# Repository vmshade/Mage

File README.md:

<!--
  This journal is auto generated by Hack Club Blueprint.
-->

# 3/29/2026 6 PM - Finished Schematic + Started PCB  

_Time spent: 0.7h_  

Wired up the schematic and made my own footprint for the USB connectivity. Decided to go for a clean and aesthetic "pcb finger" approach. Also started working on the PCB

# 3/29/2026 8:03 PM - Finished PCB + Started BOM  

_Time spent: 1.0h_  

Finished the PCB. Its only after i reviewed the dimensions did i realise this is one chonke boi. But its alright as long as it does what i need to. I took inspiration from the Waveshare rp2350 one.  

# 3/29/2026 8:48 PM - Uploaded Gerber to JLCPCB  

_Time spent: 0.5h_  

Uploaded gerber files to jlcpcb and created the bill of materials. Came out to around £57 including shipping which is crazy for something so small. :(

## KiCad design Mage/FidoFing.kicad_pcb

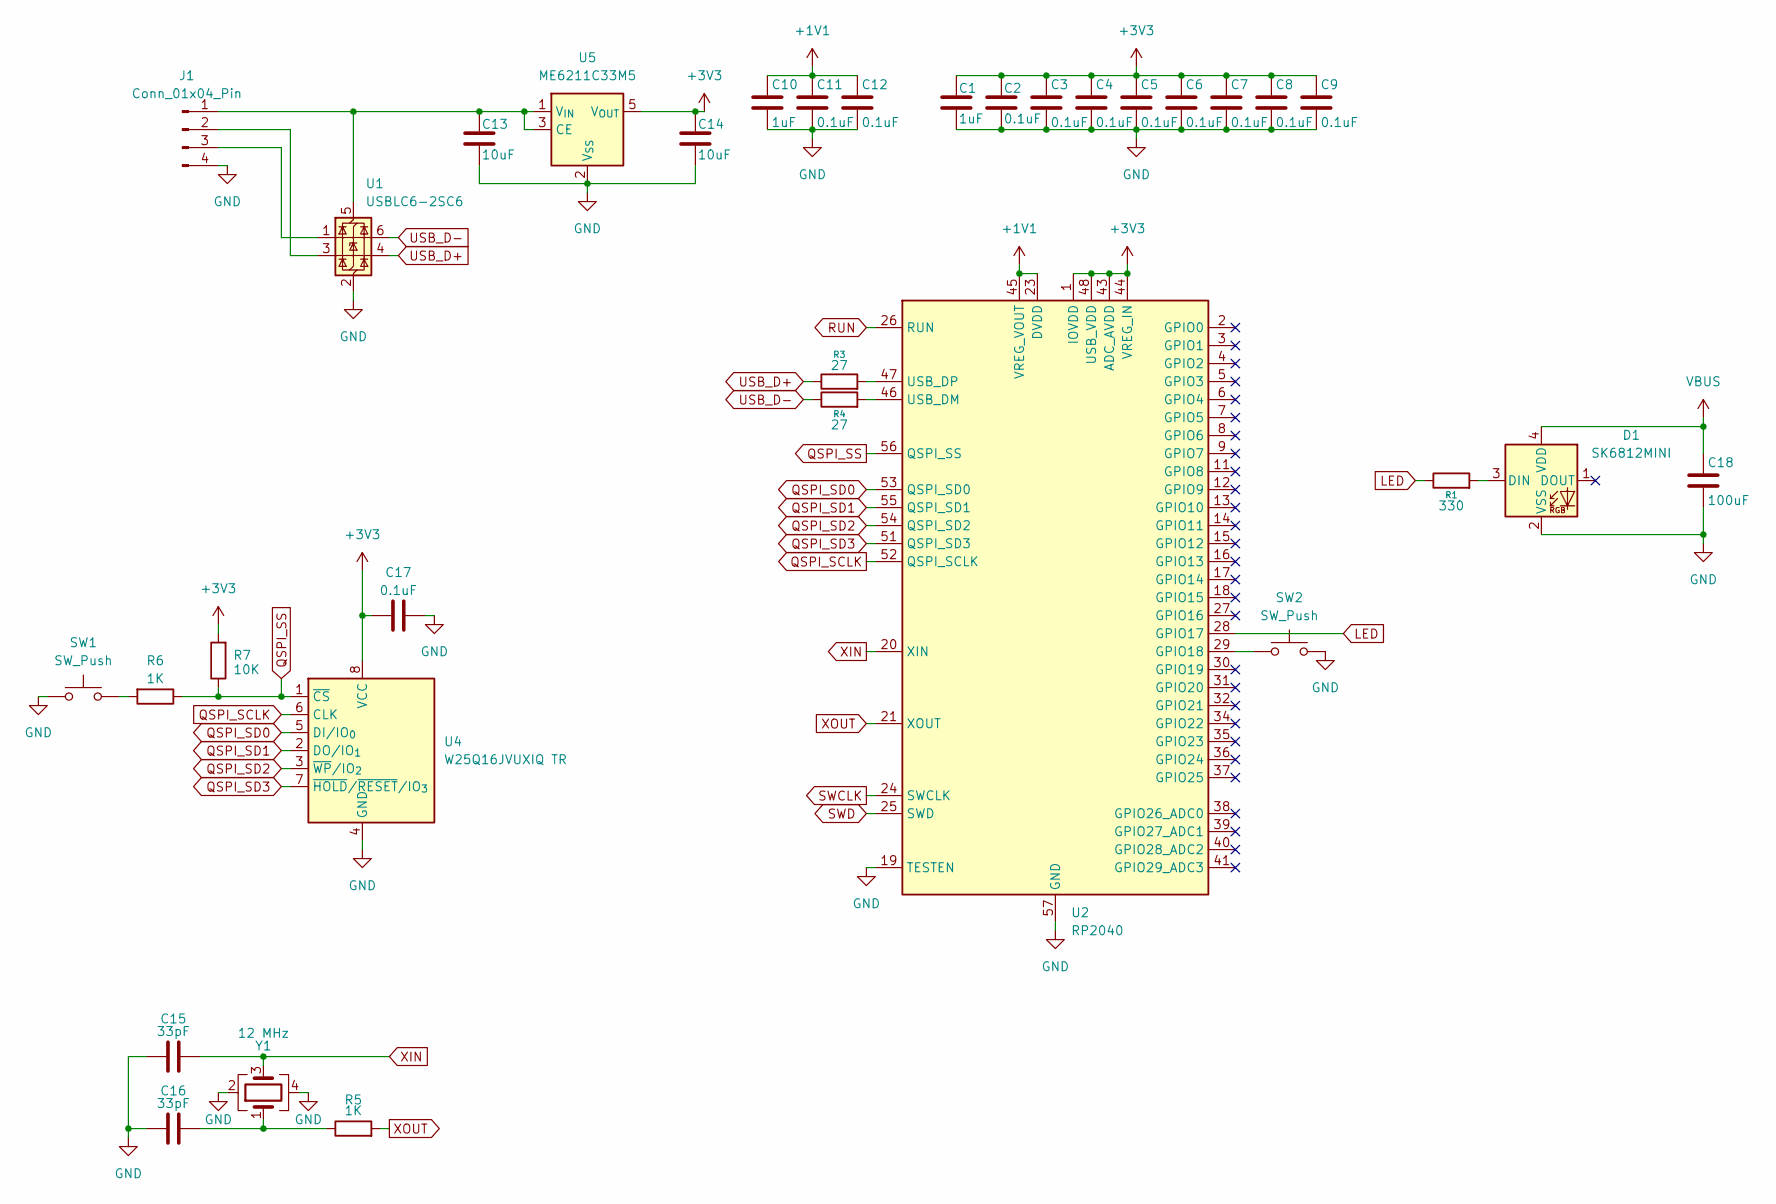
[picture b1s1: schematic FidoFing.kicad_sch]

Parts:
C1, C10: 1uF; C_0402_1005Metric
C2, C3, C4, C5, C6, C7, C8, C9, C11, C12, C17: 0.1uF; C_0402_1005Metric
C13, C14: 10uF; C_0402_1005Metric
C15, C16: 33pF; C_0402_1005Metric
C18: 100uF; C_0805_2012Metric
D1: SK6812MINI; LED_SK6812MINI_PLCC4_3.5x3.5mm_P1.75mm
J1: Conn_01x04_Pin; USB_A
R1: 330; R_0402_1005Metric
R3, R4: 27; R_0402_1005Metric
R5, R6: 1K; R_0402_1005Metric
R7: 10K; R_0402_1005Metric
SW1, SW2: SW_Push; SW_Push_SPST_NO_Alps_SKRK
U1: USBLC6-2SC6; SOT-23-6
U2: RP2040; QFN-56-1EP_7x7mm_P0.4mm_EP3.2x3.2mm
U4: W25Q16JVUXIQ TR; Winbond_USON-8-1EP_3x2mm_P0.5mm_EP0.2x1.6mm
U5: ME6211C33M5; SOT-23-5
Y1: 12 MHz; Crystal_SMD_3225-4Pin_3.2x2.5mm

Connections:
+1V1: C10.1, C11.1, C12.1, U2.23 (DVDD), U2.45 (VREG_VOUT), U2.50 (DVDD)
+3V3: C1.1, C2.1, C3.1, C4.1, C5.1, C6.1, C7.1, C8.1, C9.1, C14.1, C17.1, R7.2, U2.1 (IOVDD), U2.10 (IOVDD), U2.22 (IOVDD), U2.33 (IOVDD), U2.42 (IOVDD), U2.43 (ADC_AVDD), U2.44 (VREG_IN), U2.48 (USB_VDD), U2.49 (IOVDD), U4.8 (VCC), U5.5 (V_{OUT})
GND: C1.2, C2.2, C3.2, C4.2, C5.2, C6.2, C7.2, C8.2, C9.2, C10.2, C11.2, C12.2, C13.2, C14.2, C15.1, C16.1, C17.2, C18.2, D1.2 (VSS), J1.4, SW1.1, SW2.2, U1.2 (GND), U2.19 (TESTEN), U2.57 (GND), U4.4 (GND), U5.2 (V_{SS}), Y1.2, Y1.4
LED: R1.1, U2.28 (GPIO17)
unnamed: C16.2, R5.1, Y1.1
unnamed: D1.3 (DIN), R1.2
unnamed: C13.1, J1.1, U1.5 (VBUS), U5.1 (V_{IN}), U5.3 (CE)
unnamed: J1.2, U1.3 (I/O2)
unnamed: J1.3, U1.1 (I/O1)
unnamed: R6.2, SW1.2
unnamed: SW2.1, U2.29 (GPIO18)
unnamed: R4.2, U2.46 (USB_DM)
unnamed: R3.2, U2.47 (USB_DP)
QSPI_SCLK: U2.52 (QSPI_SCLK), U4.6 (CLK)
QSPI_SD0: U2.53 (QSPI_SD0), U4.5 (DI/IO_{0})
QSPI_SD1: U2.55 (QSPI_SD1), U4.2 (DO/IO_{1})
QSPI_SD2: U2.54 (QSPI_SD2), U4.3 (~WP/IO_{2})
QSPI_SD3: U2.51 (QSPI_SD3), U4.7 (~HOLD/~RESET/IO_{3})
QSPI_SS: R6.1, R7.1, U2.56 (QSPI_SS), U4.1 (~CS)
RUN: U2.26 (RUN)
SWCLK: U2.24 (SWCLK)
SWD: U2.25 (SWD)
USB_D+: R3.1, U1.4 (I/O2)
USB_D-: R4.1, U1.6 (I/O1)
VBUS: C18.1, D1.4 (VDD)
XIN: C15.2, U2.20 (XIN), Y1.3
XOUT: R5.2, U2.21 (XOUT)

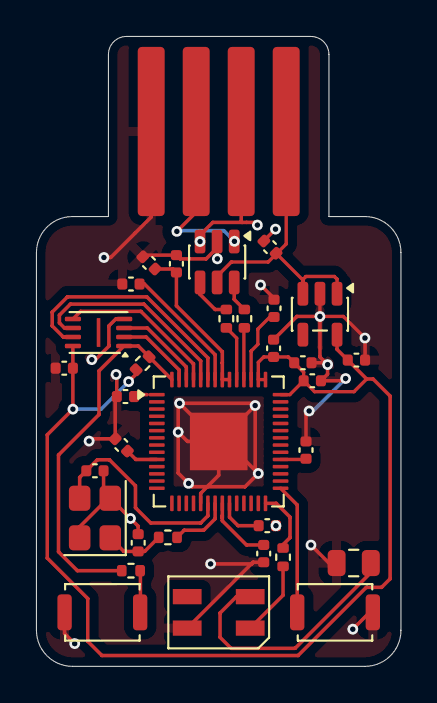
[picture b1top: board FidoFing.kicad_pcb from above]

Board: 2 copper layers, 20.3 x 35.0 mm, 33 parts (0 on the bottom side), 24 nets.

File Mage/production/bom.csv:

Designator,Footprint,Quantity,Value,LCSC Part #
"C1, C10",0402,2,1uF,
"C11, C12, C17, C2, C3, C4, C5, C6, C7, C8, C9",0402,11,0.1uF,
"C13, C14",0402,2,10uF,
"C15, C16",0402,2,33pF,
C18,0805,1,100uF,
D1,LED_SK6812MINI_PLCC4_3.5x3.5mm_P1.75mm,1,SK6812MINI,
J1,USB_A,1,Conn_01x04_Pin,
R1,0402,1,330,
"R3, R4",0402,2,27,
"R5, R6",0402,2,1K,
R7,0402,1,10K,
"SW1, SW2",SW_Push_SPST_NO_Alps_SKRK,2,SW_Push,
U1,SOT-23-6,1,USBLC6-2SC6,
U2,QFN-56-1EP_7x7mm_P0.4mm_EP3.2x3.2mm,1,RP2040,
U4,Winbond_USON-8-1EP_3x2mm_P0.5mm_EP0.2x1.6mm,1,W25Q16JVUXIQ TR,
U5,SOT-23-5,1,ME6211C33M5,
Y1,Crystal_SMD_3225-4Pin_3.2x2.5mm,1,12 MHz,
